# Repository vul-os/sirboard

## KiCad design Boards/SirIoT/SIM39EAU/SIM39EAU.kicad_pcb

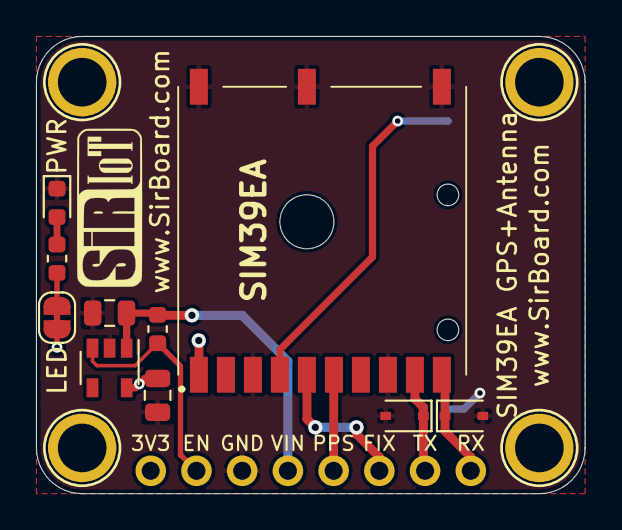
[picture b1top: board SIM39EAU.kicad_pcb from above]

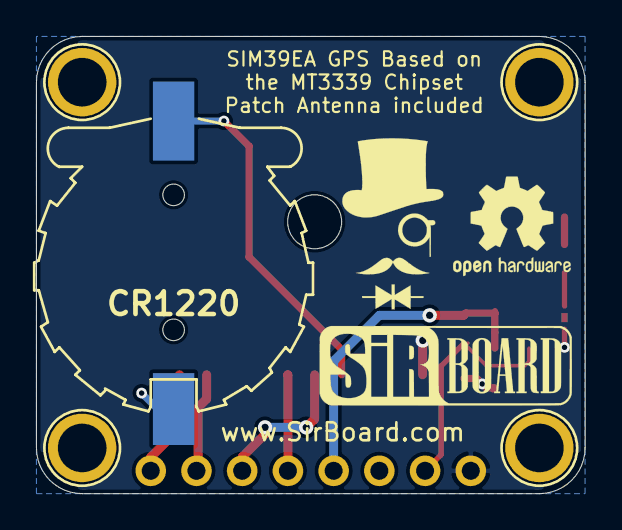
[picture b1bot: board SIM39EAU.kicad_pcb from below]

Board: 2 copper layers, 30.5 x 25.4 mm, 16 parts (2 on the bottom side), 11 nets.

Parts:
C3, C4: 10uF; C_0805_2012Metric
CR1220: CR1220; S8411-45R_1
D1, D2: TVS; D_SOD-323
H1, H2, H3, H4: MountingHole; MountingHole_M2.5_SirBoard
J1: Conn_01x08; PinHeader_1x08_P2.54mm_Vertical
LED: SolderJumper_2_Bridged; SolderJumper-2_P1.3mm_Bridged_RoundedPad1.0x1.5mm
PWR: LED; LED_0603_1608Metric
R1: 680E; R_0603_1608Metric
R3: 10K; R_0603_1608Metric
SIM39EA: SIM39EA
U1: AP2127K-3.3; SOT-23-5

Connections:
3V3: C4.1, J1.8, LED.1, SIM39EA.1, U1.5
EN: J1.7, R3.2, U1.3
FIX: J1.3, SIM39EA.5
GND: C3.2, C4.2, CR1220.2, D1.2, D2.2, J1.6, PWR.1, SIM39EA.3, SIM39EA.8, SIM39EA.11, SIM39EA.12, SIM39EA.13, U1.2
unnamed: CR1220.1, SIM39EA.4
unnamed: PWR.2, R1.1
unnamed: LED.2, R1.2
PPS: J1.4, SIM39EA.6
RX: D1.1, J1.1, SIM39EA.10
TX: D2.1, J1.2, SIM39EA.9
VIN: C3.1, J1.5, R3.1, U1.1

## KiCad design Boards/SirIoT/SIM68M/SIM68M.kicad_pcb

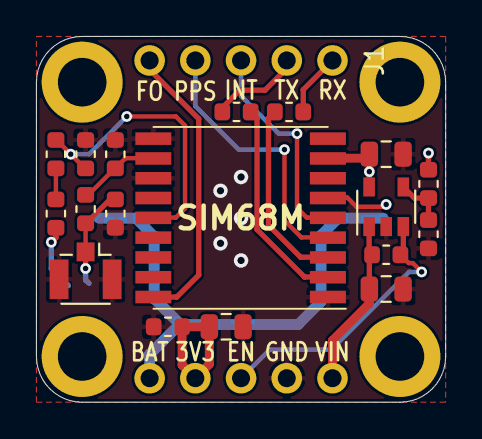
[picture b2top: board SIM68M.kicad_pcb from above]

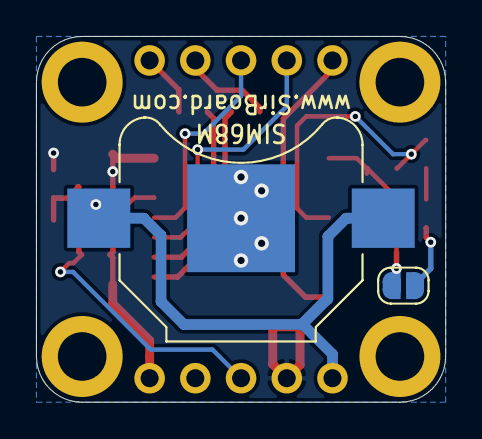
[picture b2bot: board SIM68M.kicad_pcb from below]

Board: 2 copper layers, 22.7 x 20.3 mm, 26 parts (2 on the bottom side), 18 nets.

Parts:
AE1: Antenna_Shield; U.FL_Hirose_U.FL-R-SMT-1_Vertical
C1: 4u7; C_0805_2012Metric
C2, C6: 100nF; C_0603_1608Metric
C3, C4: 1uF; C_0805_2012Metric
C5, C7: NC; C_0603_1608Metric
CR1220: Battery_Cell; BatteryHolder_Keystone_3000_1x12mm
H1, H2, H3, H4: MountingHole; MountingHole_2.7mm_M2.5_ISO14580_Pad
IC1: SIM68M; SIM28M
J1, J2: Conn_01x05; PinHeader_1x05_P2.54mm_Vertical
JP1: SolderJumper_2_Open; SolderJumper-2_P1.3mm_Open_RoundedPad1.0x1.5mm
L1: 27n; L_0603_1608Metric
R1, R2: 100R; R_0603_1608Metric
R3: 10K; R_0603_1608Metric
R4: 0R; R_0603_1608Metric
R5: 10R; R_0603_1608Metric
R7: 68K; R_0603_1608Metric
R8: 22K; R_0603_1608Metric
U2: AP7365-W-7; SOT-23-5

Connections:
3V3: C1.1, C2.1, C4.1, IC1.8, J2.4, R7.1, U2.5
EN: J2.3, R3.2, U2.3
F_O: IC1.18, J1.5
GND: AE1.2, C1.2, C2.2, C3.2, C4.2, C5.2, C6.1, C7.2, CR1220.2, IC1.1, IC1.10, IC1.12, J2.2, R8.1, U2.2
INT: IC1.5, J1.3
unnamed: AE1.1, C7.1, JP1.2, R4.2
unnamed: C5.1, IC1.11, R4.1
unnamed: C6.2, IC1.14, R5.1
unnamed: IC1.2, R2.2
unnamed: IC1.3, R1.2
unnamed: JP1.1, L1.1
unnamed: L1.2, R5.2
unnamed: R7.2, R8.2, U2.4
PPS: IC1.4, J1.4
RXD0: J1.1, R1.1
TXD0: J1.2, R2.1
VBAT: CR1220.1, IC1.6, J2.5
VIN: C3.1, J2.1, R3.1, U2.1

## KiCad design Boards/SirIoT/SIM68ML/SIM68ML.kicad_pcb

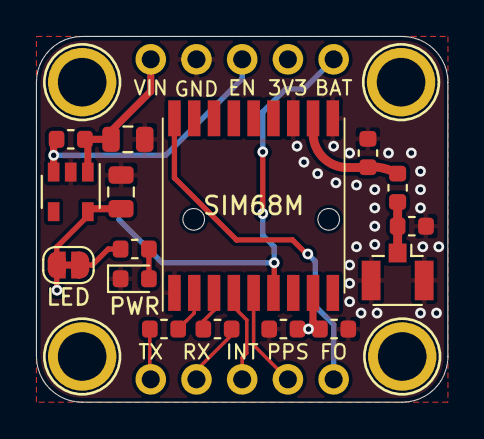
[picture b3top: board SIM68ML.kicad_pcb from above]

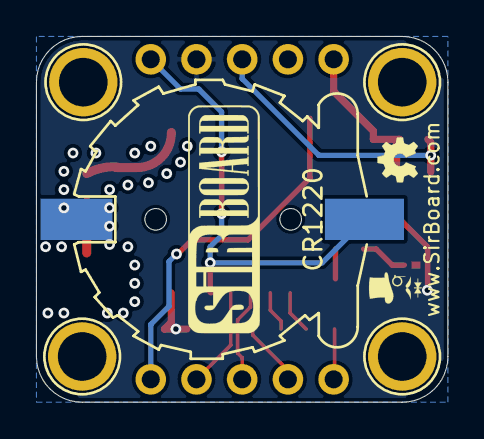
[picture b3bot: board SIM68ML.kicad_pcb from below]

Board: 2 copper layers, 22.9 x 20.3 mm, 23 parts (3 on the bottom side), 16 nets.

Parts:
AE1: Antenna_Shield; U.FL_Hirose_U.FL-R-SMT-1_Vertical
BT1: Battery_Cell; S8411-45R_1
C1: 4.7uF; C_0603_1608Metric
C2: 100nF; C_0603_1608Metric
C3, C4: 10uF; C_0805_2012Metric
C5, C7: NC; C_0603_1608Metric
H1, H2, H3, H4: MountingHole; MountingHole_M2.5_SirBoard
IC1: SIM68M; SIM28M
J1, J2: Conn_01x05; PinHeader_1x05_P2.54mm_Vertical
LED: SolderJumper_2_Bridged; SolderJumper-2_P1.3mm_Bridged_RoundedPad1.0x1.5mm
PWR: LED; LED_0603_1608Metric
R1, R2: 100R; R_0603_1608Metric
R3: 10K; R_0603_1608Metric
R4: 0R; R_0603_1608Metric
R6: 680E; R_0603_1608Metric
U1: AP2127K-3.3; SOT-23-5

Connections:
3V3: C1.1, C2.1, C4.1, IC1.8, J2.4, LED.1, U1.5
/ANT: C5.1, IC1.11, R4.1
EN: J2.3, R3.2, U1.3
F_O: IC1.18, J1.5
GND: AE1.2, BT1.2, C1.2, C2.2, C3.2, C4.2, C5.2, C7.2, IC1.1, IC1.10, IC1.12, J2.2, PWR.1, U1.2
INT: IC1.5, J1.4
unnamed: AE1.1, C7.1, R4.2
unnamed: PWR.2, R6.1
unnamed: IC1.2, R2.2
unnamed: IC1.3, R1.2
unnamed: LED.2, R6.2
PPS: IC1.4, J1.3
RXD0: J1.2, R1.1
TXD0: J1.1, R2.1
VBAT: BT1.1, IC1.6, J2.5
VIN: C3.1, J2.1, R3.1, U1.1

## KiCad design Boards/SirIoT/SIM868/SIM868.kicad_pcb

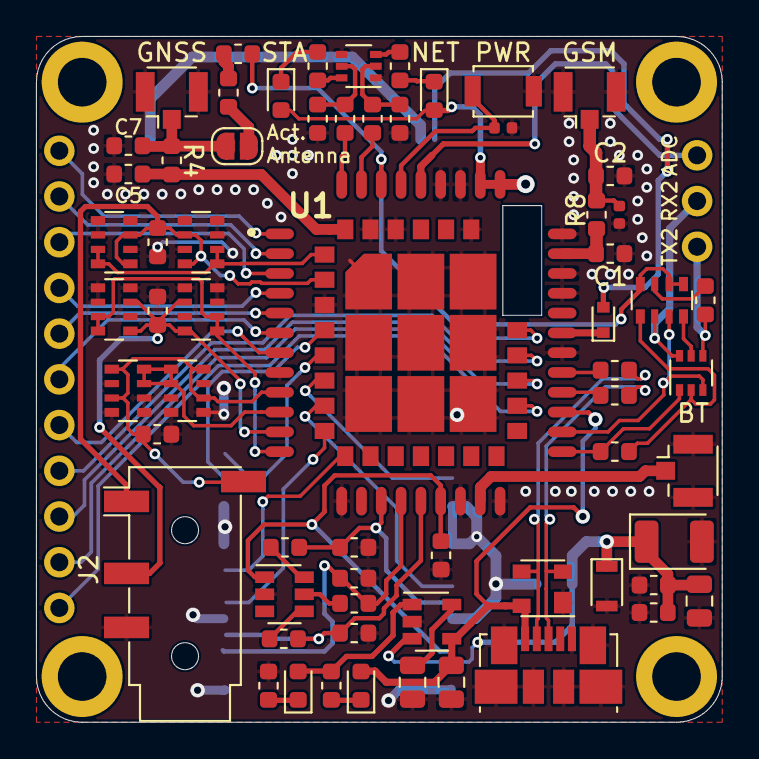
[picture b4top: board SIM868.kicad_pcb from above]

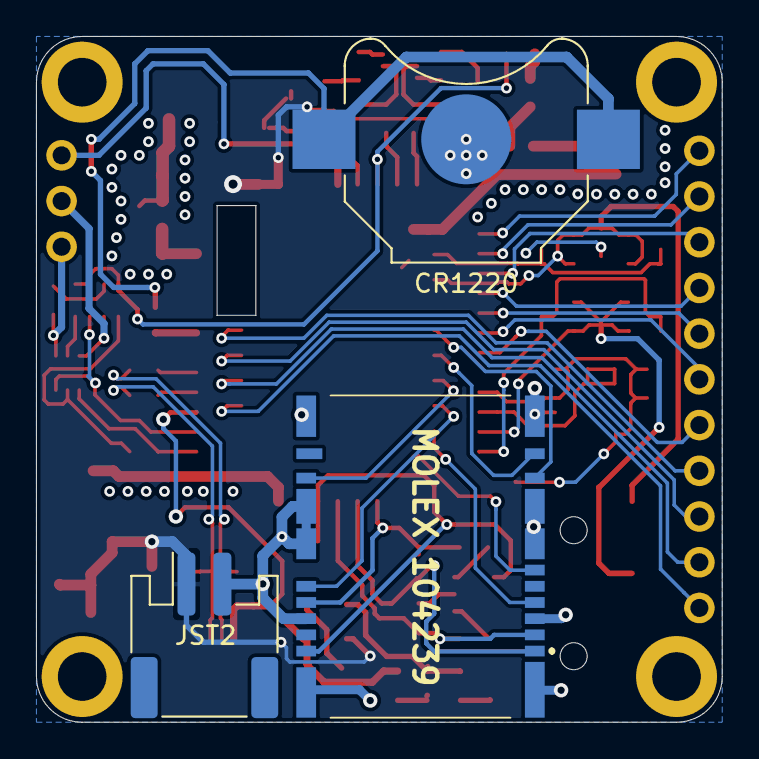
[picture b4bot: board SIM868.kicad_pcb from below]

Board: 2 copper layers, 38.1 x 38.1 mm, 73 parts (5 on the bottom side), 68 nets.

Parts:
BT: Antenna_Shield; U.FL_Hirose_U.FL-R-SMT-1_Vertical
C1, C2, C5, C7: NC; C_0603_1608Metric
C3: 100nF; C_0603_1608Metric
C4: 100uF; CP_EIA-3528-21_Kemet-B
C6: 10uF; C_0805_2012Metric
C8: 33pF; C_0603_1608Metric
C9: 10pF; C_0603_1608Metric
C10, C11, C12: 22pF; C_0603_1608Metric
C13: 1uF; C_0805_2012Metric
CN1, CN2, CN3: 10pF; R_Array_Convex_4x0603
CN4, CN5, CN6: 33pF; R_Array_Convex_4x0603
CR1220: CR1025; BatteryHolder_Keystone_3000_1x12mm
D1: ESDA6V1-5SC6; SOT-23-6
D3: D_Schottky; D_SOD-523
D5: ORANGE; LED_0603_1608Metric
D6: GREEN; LED_0603_1608Metric
D7: PRTR5V0U2X; SOT-143
D9, D11, D13: BDFN1C031V; C_0603_1608Metric
GNSS: Antenna_Shield; U.FL_Hirose_U.FL-R-SMT-1_Vertical
GSM: Antenna_Shield; U.FL_Hirose_U.FL-R-SMT-1_Vertical
H1, H2, H3, H4: MountingHole; MountingHole_2.7mm_M2.5_ISO14580_Pad
J2: AudioJack4; Jack_3.5mm_PJ320D_Horizontal
J4: USB_B_Micro; USB_Micro-B_Molex_47346-0001
J5: Conn_01x11; PinHeader_1x11_P2.54mm_Vertical
J6: Conn_01x03; PinHeader_1x03_P2.54mm_Vertical
JP1: SolderJumper_2_Open; SolderJumper-2_P1.3mm_Open_RoundedPad1.0x1.5mm
JST2: Conn_01x02; JST_PH_S2B-PH-SM4-TB_1x02-1MP_P2.00mm_Horizontal
L1: 27n; L_0603_1608Metric
MOLEX 104239: MOLEX 104239-1430; 1042391430
NET: WHITE; LED_0603_1608Metric
PWR: B3U-1000P; SW_SPST_B3U-1000P
Q1, Q2: BC847BDW1; SOT-363_SC-70-6
R1, R6, R13, R16: 47K; R_0603_1608Metric
R2: 2K; R_0805_2012Metric
R3, R14, R17: 1K; R_0603_1608Metric
R4, R8: 0R; R_0603_1608Metric
R5: 10R; R_0603_1608Metric
R7: 470E; R_0603_1608Metric
R9, R10, R11: 51E; R_0603_1608Metric
R12, R15: 4K7; R_0603_1608Metric
R18, R19: 22E; R_0603_1608Metric
RN2: 4k7; R_Array_Convex_4x0603
STA: WHITE; LED_0603_1608Metric
TVS1, TVS2: LXES15AAA1-153; R_0402_1005Metric
U1: SIM868
U2: MCP73831-2-OT; SOT-23-5
Z1: PZ3D4V2H; D_SOD-323F

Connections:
5V: R6.2, RN2.7
/BT: BT.1, U1.20
/uD+: R18.1, U1.25
/uD-: R19.1, U1.26
ADC: J6.3, U1.38
D+: D7.2, J4.3, R18.2
D-: D7.3, J4.2, R19.2
GND: BT.2, C1.2, C2.2, C3.2, C4.2, C5.2, C6.2, C7.2, C8.2, C9.2, C10.2, C11.2, C12.2, C13.2, CN1.2, CN1.4, CN1.5, CN1.6, CN2.2, CN2.4, CN2.5, CN2.6, CN3.2, CN3.4, CN3.5, CN3.6, CN4.3, CN4.4, CN4.5, CN4.7, CN5.3, CN5.4, CN5.5, CN5.7, CN6.3, CN6.4, CN6.5, CN6.7, CR1220.2, D1.2, D7.1, D9.1, D11.1, D13.1, GNSS.2, GSM.2, J2.R2, J4.5, J4.6, JST2.2, MOLEX 104239.4, MOLEX 104239.12, MOLEX 104239.15, MOLEX 104239.16, MOLEX 104239.17, MOLEX 104239.18, MOLEX 104239.19, MOLEX 104239.20, MOLEX 104239.21, MOLEX 104239.22, PWR.1, Q2.1, Q2.4, R2.1, R3.2, R13.1, R16.1, TVS1.1, TVS2.1, U1.8, U1.13, U1.19, U1.21, U1.27, U1.30, U1.31, U1.33, U1.36, U1.37, U1.45, U1.63, U1.66, U1.67, U1.69, U1.70, U1.71, U1.72, U1.73, U1.74, U1.75, U1.76, U1.77, U2.2, Z1.2
GNSS_ANT: C5.1, R4.1, U1.68
GNSS_EN: J5.11, U1.59
GNSS_RX: J5.8, U1.62
GNSS_TX: J5.9, U1.61
GSM_ANT: C1.1, R8.1, U1.32
MIC+: CN1.1, CN1.3, CN4.6, CN4.8, D11.2, J2.S, U1.9
MIC-: CN1.7, CN1.8, CN4.1, CN4.2, U1.10
NET_L: R12.2, U1.41
unnamed: C7.1, GNSS.1, JP1.2, R4.2
unnamed: C2.1, GSM.1, R8.2, TVS2.2
unnamed: CR1220.1, D3.2
unnamed: D1.4, R9.1
unnamed: D1.5, R10.1
unnamed: D1.6, R11.1
unnamed: R14.2, STA.1
unnamed: D3.1, U1.28
unnamed: NET.1, R17.2
unnamed: D5.1, R7.2
unnamed: D6.1, R3.1
unnamed: D6.2, R7.1, U2.1
unnamed: JP1.1, L1.1
unnamed: L1.2, R5.2
unnamed: Q1.2, R1.2, RN2.1
unnamed: Q1.5, RN2.4
unnamed: Q2.2, R12.1, R13.2
unnamed: Q2.3, R17.1
unnamed: Q2.5, R15.1, R16.2
unnamed: Q2.6, R14.1
unnamed: R2.2, U2.5
PPS: J5.10, U1.60
PWR_KEY: PWR.2, TVS1.2, U1.39
RX_5V: J6.2, Q1.6, RN2.2
SD_CLK: MOLEX 104239.11, U1.50
SD_CMD: MOLEX 104239.9, U1.51
SD_DATA0: MOLEX 104239.13, U1.49
SD_DATA1: MOLEX 104239.14, U1.48
SD_DATA2: MOLEX 104239.7, U1.47
SD_DATA3: MOLEX 104239.8, U1.46
SIM_CLK: C11.1, MOLEX 104239.1, R10.2, U1.16
SIM_IO: C10.1, MOLEX 104239.6, R11.2, U1.15
SIM_RST: C12.1, MOLEX 104239.2, R9.2, U1.17
SIM_VDD: C3.1, D1.1, MOLEX 104239.3, U1.18
SPK1+: CN2.1, CN2.3, CN5.6, CN5.8, D9.2, J2.R1, U1.11
SPK1-: CN2.7, CN2.8, CN5.1, CN5.2, U1.12
SPK2+: CN3.1, CN3.3, CN6.6, CN6.8, D13.2, J2.T, U1.44
SPK2-: CN3.7, CN3.8, CN6.1, CN6.2, U1.43
STA_L: R15.2, U1.42
TX_5V: J6.1, Q1.4, R6.1
UART1_CTS: J5.4, U1.4
UART1_DCD: J5.5, U1.5
UART1_DTR: J5.6, U1.6
UART1_RI: J5.7, U1.7
UART1_RTS: J5.3, U1.3
UART1_RX: J5.2, U1.2
UART1_TX: J5.1, U1.1
UART2_RX: Q1.3, RN2.3, U1.23
UART2_TX: Q1.1, R1.1, U1.22
VBAT: C4.1, C6.1, C8.1, C9.1, JST2.1, NET.2, STA.2, U1.34, U1.35, U2.3, Z1.1
VBUS: C13.1, D5.2, D7.4, J4.1, U1.24, U2.4
VCC_EXT: R5.1, RN2.5, RN2.6, RN2.8, U1.40

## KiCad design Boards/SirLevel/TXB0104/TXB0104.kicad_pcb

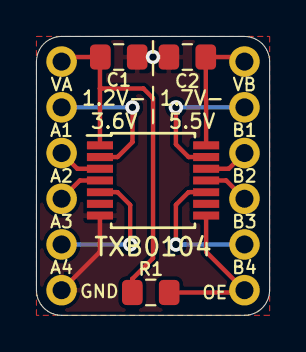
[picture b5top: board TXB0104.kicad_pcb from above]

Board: 2 copper layers, 13.0 x 15.5 mm, 6 parts (0 on the bottom side), 12 nets.

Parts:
C1, C2: 100nF; C_0805_2012Metric_Pad1.15x1.40mm_HandSolder
J1, J2: Conn_01x06; PinHeader_1x06_P2.54mm_Vertical
R1: 10k; R_0805_2012Metric_Pad1.15x1.40mm_HandSolder
TXB0104: TXB0104PW; TSSOP-14_4.4x5mm_P0.65mm

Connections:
/A1: J1.2, TXB0104.2
/A2: J1.3, TXB0104.3
/A3: J1.4, TXB0104.4
/A4: J1.5, TXB0104.5
/B1: J2.2, TXB0104.13
/B2: J2.3, TXB0104.12
/B3: J2.4, TXB0104.11
/B4: J2.5, TXB0104.10
/GND: C1.1, C2.1, J1.6, TXB0104.7
/OE: J2.6, R1.2, TXB0104.8
/VHI: C2.2, J2.1, TXB0104.14
/VLOW: C1.2, J1.1, R1.1, TXB0104.1

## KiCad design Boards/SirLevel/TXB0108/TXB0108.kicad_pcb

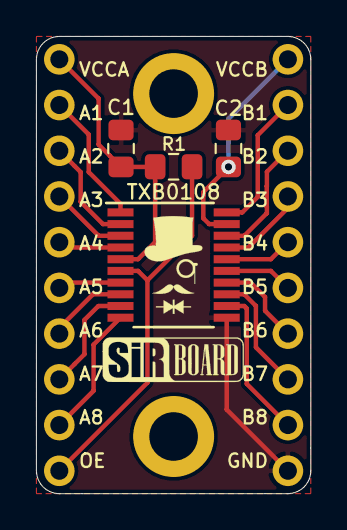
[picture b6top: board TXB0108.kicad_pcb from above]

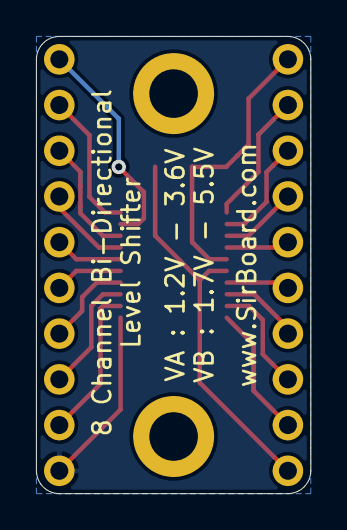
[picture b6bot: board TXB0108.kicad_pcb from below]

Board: 2 copper layers, 15.2 x 25.4 mm, 6 parts (2 on the bottom side), 20 nets.

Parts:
C1, C2: 100n; C_0805_2012Metric_Pad1.15x1.40mm_HandSolder
J1, J2: Conn_01x10; PinHeader_1x10_P2.54mm_Vertical
R1: 4k7; R_0805_2012Metric_Pad1.15x1.40mm_HandSolder
TXB0108: TXB0108DQSR; TSSOP-20_4.4x6.5mm_P0.65mm

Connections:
/A1: J1.2, TXB0108.1
/A2: J1.3, TXB0108.2
/A3: J1.4, TXB0108.3
/A4: J1.5, TXB0108.4
/A5: J1.6, TXB0108.7
/A6: J1.7, TXB0108.8
/A7: J1.8, TXB0108.9
/A8: J1.9, TXB0108.10
/B1: J2.2, TXB0108.20
/B2: J2.3, TXB0108.18
/B3: J2.4, TXB0108.17
/B4: J2.5, TXB0108.16
/B5: J2.6, TXB0108.15
/B6: J2.7, TXB0108.14
/B7: J2.8, TXB0108.13
/B8: J2.9, TXB0108.12
/GND: C1.1, C2.1, J2.10, TXB0108.11
/OE: J1.10, R1.2, TXB0108.6
/VccA: C1.2, J1.1, R1.1, TXB0108.5
/VccB: C2.2, J2.1, TXB0108.19

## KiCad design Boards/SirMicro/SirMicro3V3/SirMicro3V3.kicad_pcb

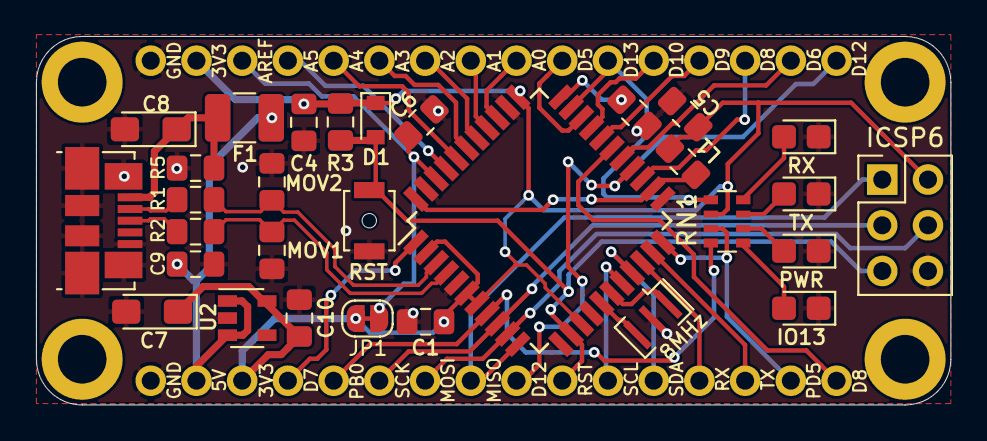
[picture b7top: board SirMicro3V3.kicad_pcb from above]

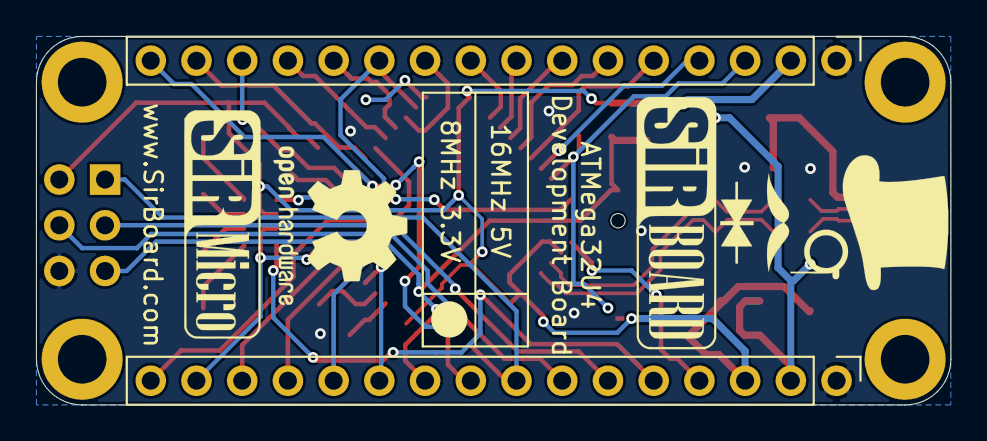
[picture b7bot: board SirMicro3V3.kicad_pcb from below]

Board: 2 copper layers, 50.8 x 20.5 mm, 32 parts (2 on the bottom side), 42 nets.

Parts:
8MHz: Resonator; Resonator_SMD_muRata_CSTxExxV-3Pin_3.0x1.1mm
C1, C9, C10: 1uF; C_0805_2012Metric_Pad1.15x1.40mm_HandSolder
C4, C5, C6: 100nF; C_0805_2012Metric_Pad1.15x1.40mm_HandSolder
C7: 1uF; CP_EIA-3216-18_Kemet-A_Pad1.58x1.35mm_HandSolder
C8: 22uF; CP_EIA-3216-18_Kemet-A_Pad1.58x1.35mm_HandSolder
D1: D; D_SOD-110
F1: 500mA; R_1210_3225Metric_Pad1.42x2.65mm_HandSolder
ICSP6: Conn_02x03_Odd_Even; PinHeader_2x03_P2.54mm_Vertical
IO13: LED; LED_0805_2012Metric_Castellated
J1, J2: Conn_01x16; PinHeader_1x16_P2.54mm_Vertical
J3: USB_B_Micro; USB_Micro-B_Molex_47346-0001
JP1: SolderJumper_2_Bridged; SolderJumper-2_P1.3mm_Bridged_RoundedPad1.0x1.5mm
L1: 10uH; L_0805_2012Metric_Pad1.15x1.40mm_HandSolder
MOV1, MOV2: 5V; R_0805_2012Metric_Pad1.15x1.40mm_HandSolder
PWR: LED; LED_0805_2012Metric_Castellated
R1, R2, R4: 22e; R_0805_2012Metric_Pad1.15x1.40mm_HandSolder
R3, R5: 10k; R_0805_2012Metric_Pad1.15x1.40mm_HandSolder
RN1: 1k; R_Array_Convex_4x0603
RST: SW_Push; SW_SPST_B3U-1000P-B
RX: LED; LED_0805_2012Metric_Castellated
TX: LED; LED_0805_2012Metric_Castellated
U1: ATmega32U4-AU; TQFP-44_10x10mm_P0.8mm
U2: AP2127K-3.3; SOT-23-5

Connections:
3V3: C1.1, C4.1, C5.1, C7.1, C10.1, D1.1, ICSP6.2, J1.2, J2.3, JP1.1, L1.1, R3.1, RN1.2, U1.2, U1.6, U1.7, U1.14, U1.34, U2.5
5V: C9.1, F1.1, J2.2, U2.1, U2.3
/D+: J3.3, R2.1
/D-: J3.2, R1.1
/HWB: R4.1, U1.33
/Vbus: C8.1, F1.2, J3.1, R5.1
/X1: 8MHz.1, U1.17
/X2: 8MHz.3, U1.16
/uD+: MOV1.1, R2.2, U1.4
/uD-: MOV2.1, R1.2, U1.3
A0: J1.9, U1.36
A1: J1.8, U1.37
A2: J1.7, U1.38
A3: J1.6, U1.39
A4: J1.5, U1.40
A5: J1.4, U1.41
AREF: C6.1, J1.3, JP1.2, U1.42
D4: J1.14, U1.25
D5: J1.10, U1.31
D6: J1.15, U1.27
D7: J2.4, U1.1
D8: J2.16, U1.28
D9: J1.13, U1.29
D10: J1.12, U1.30
D12: J1.16, J2.9, U1.26
D13: J1.11, RN1.1, U1.32
GND: 8MHz.2, C1.2, C4.2, C5.2, C6.2, C7.2, C8.2, C9.2, C10.2, ICSP6.6, IO13.1, J1.1, J2.1, J3.5, J3.6, MOV1.2, MOV2.2, PWR.1, R4.2, R5.2, RST.1, RX.1, TX.1, U1.5, U1.15, U1.23, U1.35, U1.43, U2.2
MISO: ICSP6.1, J2.8, U1.11
MOSI: ICSP6.4, J2.7, U1.10
unnamed: IO13.2, RN1.5
unnamed: L1.2, U1.24, U1.44
unnamed: PWR.2, RN1.6
unnamed: RN1.7, TX.2
unnamed: RN1.8, RX.2
RST: D1.2, ICSP6.5, J2.10, R3.2, RST.2, U1.13
RX: J2.13, U1.20
RXLED: J2.5, RN1.4, U1.8
SCK: ICSP6.3, J2.6, U1.9
SCL: J2.11, U1.18
SDA: J2.12, U1.19
TX: J2.14, U1.21
TXLED: J2.15, RN1.3, U1.22
